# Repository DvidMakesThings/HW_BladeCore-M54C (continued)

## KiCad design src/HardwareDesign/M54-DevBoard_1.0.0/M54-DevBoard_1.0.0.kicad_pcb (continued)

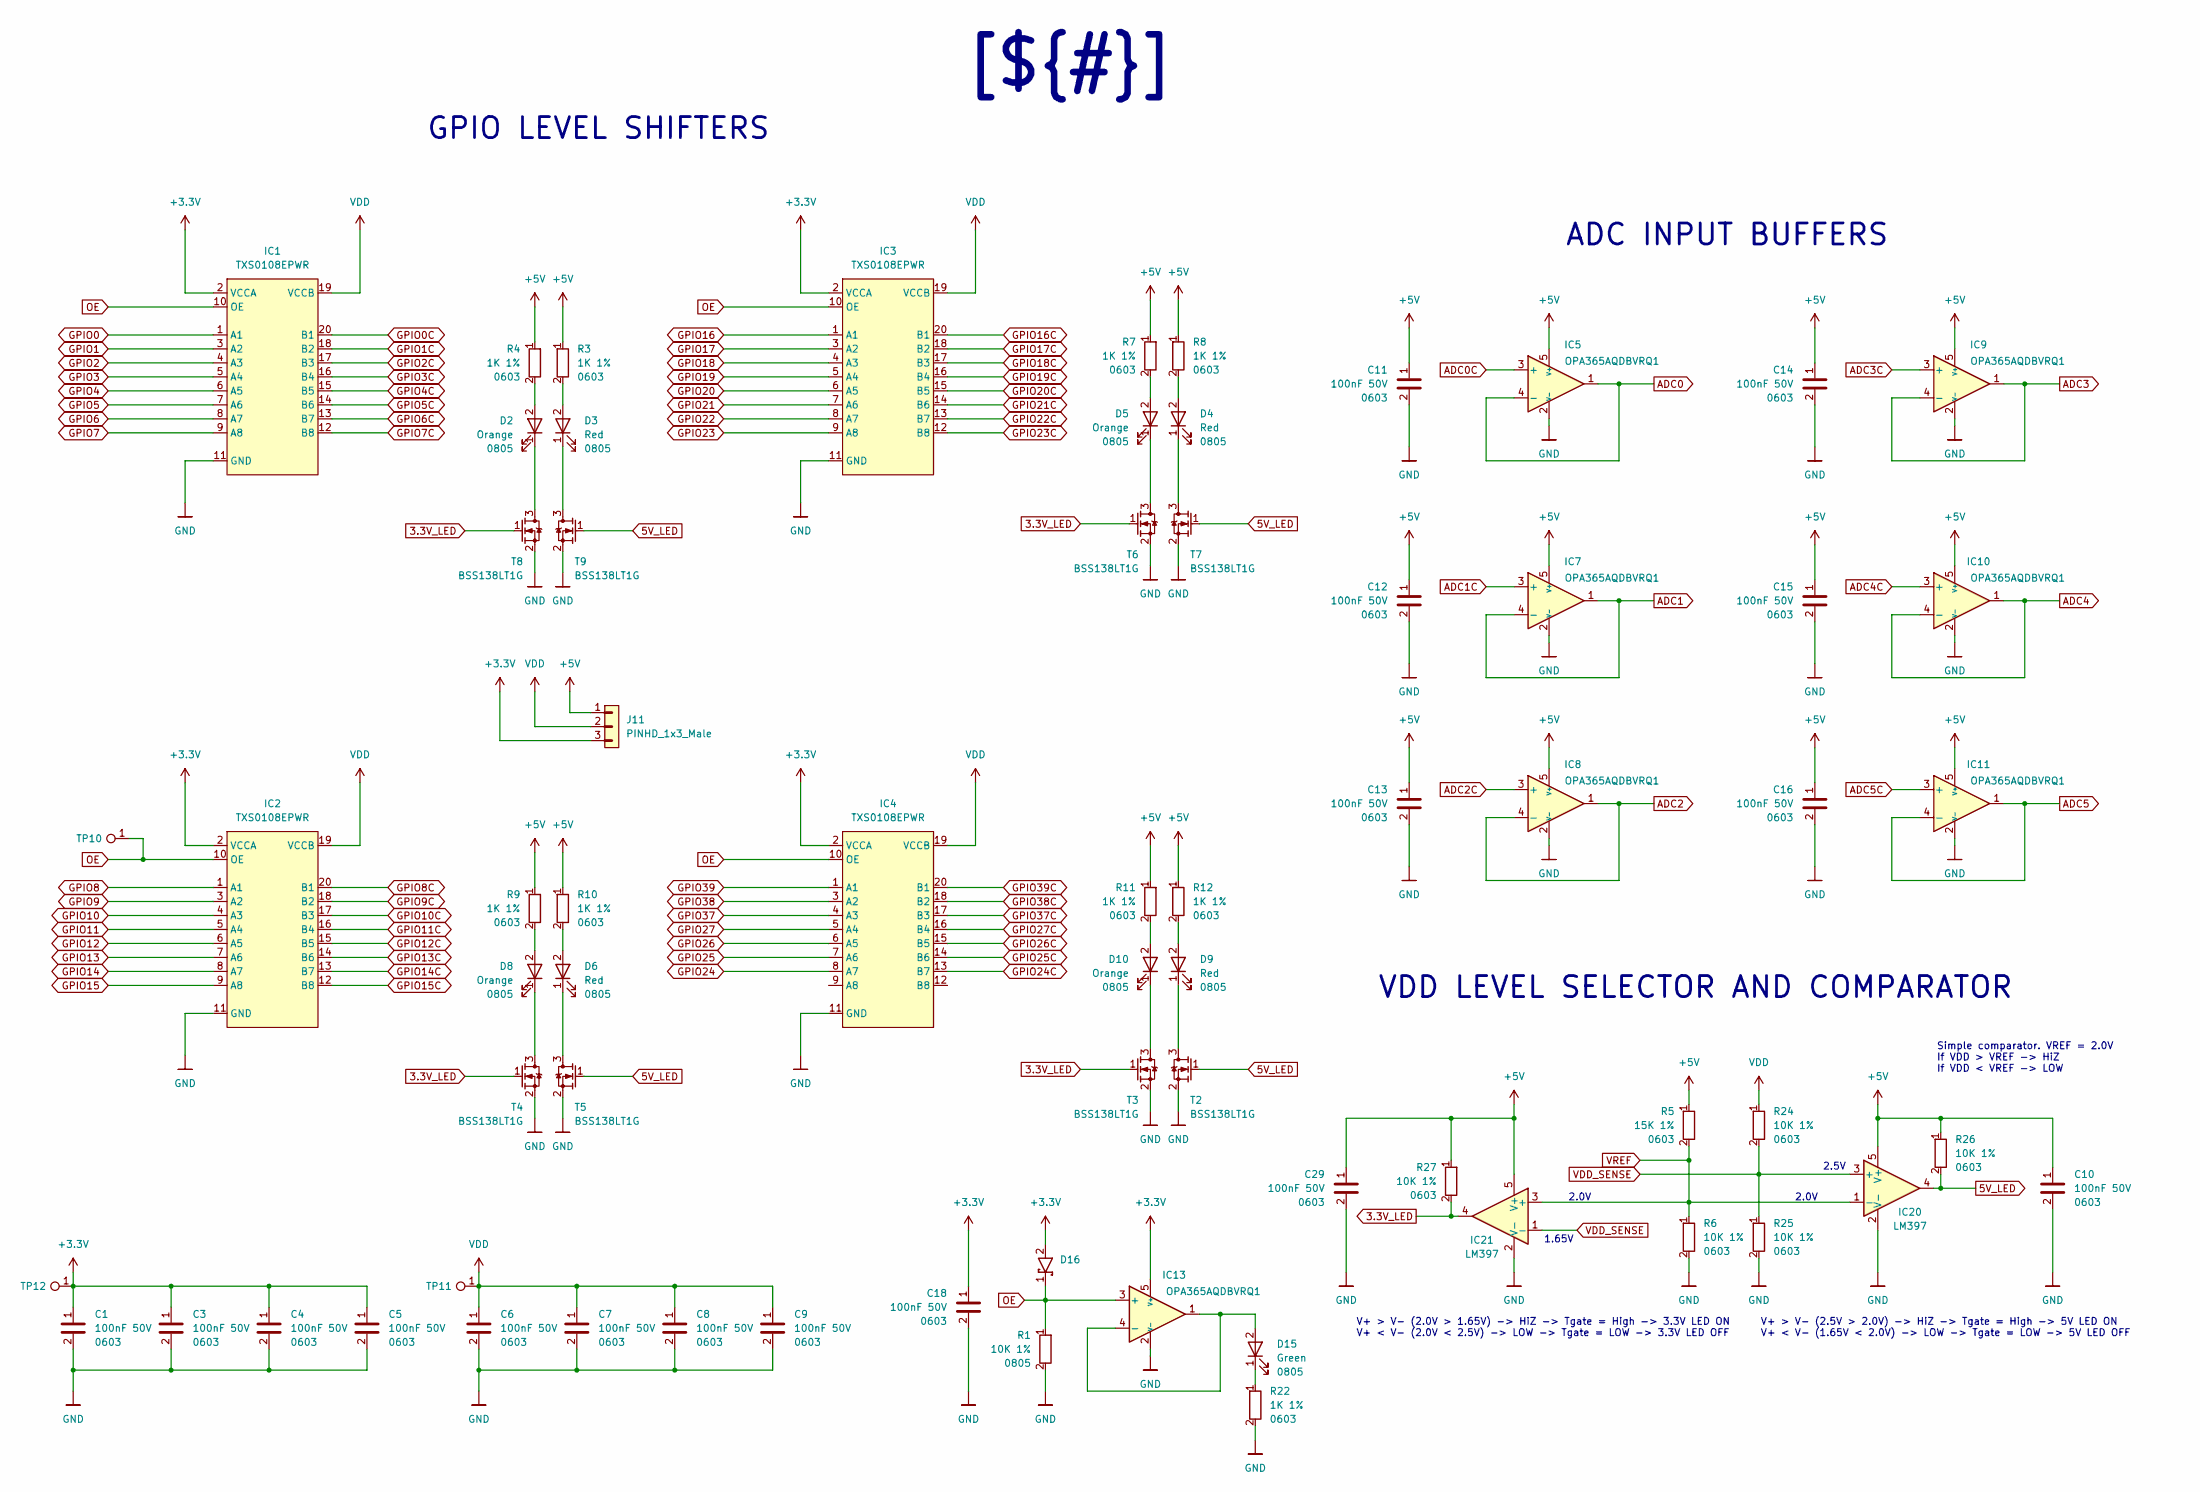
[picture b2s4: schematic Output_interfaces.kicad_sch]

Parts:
C1, C3, C4, C5, C6, C7, C8, C9, C10, C11, C12, C13, C14, C15, C16, C18, C29: 100nF 50V; C_0603_1608Metric; LCSC_PART C14663
D2, D5, D8, D10: Orange; LED_0805_2012Metric; MPN XL-2012UOC; LCSC_PART C965813
D3, D4, D6, D9: Red; LED_0805_2012Metric; MPN XL-2012VRC; LCSC_PART C7371913
D15: Green; LED_0805_2012Metric; MPN XL-2012UGC; LCSC_PART C965815
D16: SMA
IC1, IC2, IC3, IC4: TXS0108EPWR; TSSOP-20_4.4x6.5_P0.65mm; MPN TXS0108EPWR; LCSC_PART C17206
IC5, IC7, IC8, IC9, IC10, IC11, IC13: OPA365AQDBVRQ1; SOT-23-5; MPN OPA365AQDBVRQ1; LCSC_PART C485978
IC20, IC21: LM397; SOT-23-5
J11: PINHD_1x3_Male; PinHeader_1x03_P2.54mm_Vertical
R1: 10K 1%; R_0805_2012Metric; LCSC_PART C17414
R3, R4, R7, R8, R9, R10, R11, R12, R22: 1K 1%; R_0603_1608Metric; LCSC_PART C21190
R5: 15K 1%; R_0603_1608Metric; LCSC_PART C22809
R6, R24, R25, R26, R27: 10K 1%; R_0603_1608Metric; LCSC_PART C25804
T2, T3, T4, T5, T6, T7, T8, T9: BSS138LT1G; SOT-23; MPN BSS138LT1G
TP10, TP11, TP12: TestPoint_0.6mm

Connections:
3.3V_LED: IC21.4, R27.2, T3.1, T4.1, T6.1, T8.1
5V_LED: IC20.4, R26.2, T2.1, T5.1, T7.1, T9.1
+3.3V: C1.1, C3.1, C4.1, C5.1, C18.1, D16.2 (A), IC1.2 (VCCA), IC2.2 (VCCA), IC3.2 (VCCA), IC4.2 (VCCA), IC13.5 (V+), J11.3, TP12.1; also elsewhere on the board
+5V: C10.1, C11.1, C12.1, C13.1, C14.1, C15.1, C16.1, C29.1, IC5.5 (V+), IC7.5 (V+), IC8.5 (V+), IC9.5 (V+), IC10.5 (V+), IC11.5 (V+), IC20.5 (V+), IC21.5 (V+), J11.1, R3.1, R4.1, R5.1, R7.1, R8.1, R9.1, R10.1, R11.1, R12.1, R26.1, R27.1; also elsewhere on the board
ADC0: IC5.1, IC5.4 (-); also elsewhere on the board
ADC0C: IC5.3 (+); also elsewhere on the board
ADC1: IC7.1, IC7.4 (-); also elsewhere on the board
ADC1C: IC7.3 (+); also elsewhere on the board
ADC2: IC8.1, IC8.4 (-); also elsewhere on the board
ADC2C: IC8.3 (+); also elsewhere on the board
ADC3: IC9.1, IC9.4 (-); also elsewhere on the board
ADC3C: IC9.3 (+); also elsewhere on the board
ADC4: IC10.1, IC10.4 (-); also elsewhere on the board
ADC4C: IC10.3 (+); also elsewhere on the board
ADC5: IC11.1, IC11.4 (-); also elsewhere on the board
ADC5C: IC11.3 (+); also elsewhere on the board
GND: C1.2, C3.2, C4.2, C5.2, C6.2, C7.2, C8.2, C9.2, C10.2, C11.2, C12.2, C13.2, C14.2, C15.2, C16.2, C18.2, C29.2, IC1.11 (GND), IC2.11 (GND), IC3.11 (GND), IC4.11 (GND), IC5.2 (V-), IC7.2 (V-), IC8.2 (V-), IC9.2 (V-), IC10.2 (V-), IC11.2 (V-), IC13.2 (V-), IC20.2 (V-), IC21.2 (V-), R1.2, R6.2, R22.2, R25.2, T2.2, T3.2, T4.2, T5.2, T6.2, T7.2, T8.2, T9.2; also elsewhere on the board
GPIO0: IC1.1 (A1); also elsewhere on the board
GPIO0C: IC1.20 (B1); also elsewhere on the board
GPIO1: IC1.3 (A2); also elsewhere on the board
GPIO1C: IC1.18 (B2); also elsewhere on the board
GPIO2: IC1.4 (A3); also elsewhere on the board
GPIO2C: IC1.17 (B3); also elsewhere on the board
GPIO3: IC1.5 (A4); also elsewhere on the board
GPIO3C: IC1.16 (B4); also elsewhere on the board
GPIO4: IC1.6 (A5); also elsewhere on the board
GPIO4C: IC1.15 (B5); also elsewhere on the board
GPIO5: IC1.7 (A6); also elsewhere on the board
GPIO5C: IC1.14 (B6); also elsewhere on the board
GPIO6: IC1.8 (A7); also elsewhere on the board
GPIO6C: IC1.13 (B7); also elsewhere on the board
GPIO7: IC1.9 (A8); also elsewhere on the board
GPIO7C: IC1.12 (B8); also elsewhere on the board
GPIO8: IC2.1 (A1); also elsewhere on the board
GPIO8C: IC2.20 (B1); also elsewhere on the board
GPIO9: IC2.3 (A2); also elsewhere on the board
GPIO9C: IC2.18 (B2); also elsewhere on the board
GPIO10: IC2.4 (A3); also elsewhere on the board
GPIO10C: IC2.17 (B3); also elsewhere on the board
GPIO11: IC2.5 (A4); also elsewhere on the board
GPIO11C: IC2.16 (B4); also elsewhere on the board
GPIO12: IC2.6 (A5); also elsewhere on the board
GPIO12C: IC2.15 (B5); also elsewhere on the board
GPIO13: IC2.7 (A6); also elsewhere on the board
GPIO13C: IC2.14 (B6); also elsewhere on the board
GPIO14: IC2.8 (A7); also elsewhere on the board
GPIO14C: IC2.13 (B7); also elsewhere on the board
GPIO15: IC2.9 (A8); also elsewhere on the board
GPIO15C: IC2.12 (B8); also elsewhere on the board
GPIO16: IC3.1 (A1); also elsewhere on the board
GPIO16C: IC3.20 (B1); also elsewhere on the board
GPIO17: IC3.3 (A2); also elsewhere on the board
GPIO17C: IC3.18 (B2); also elsewhere on the board
GPIO18: IC3.4 (A3); also elsewhere on the board
GPIO18C: IC3.17 (B3); also elsewhere on the board
GPIO19: IC3.5 (A4); also elsewhere on the board
GPIO19C: IC3.16 (B4); also elsewhere on the board
GPIO20: IC3.6 (A5); also elsewhere on the board
GPIO20C: IC3.15 (B5); also elsewhere on the board
GPIO21: IC3.7 (A6); also elsewhere on the board
GPIO21C: IC3.14 (B6); also elsewhere on the board
GPIO22: IC3.8 (A7); also elsewhere on the board
GPIO22C: IC3.13 (B7); also elsewhere on the board
GPIO23: IC3.9 (A8); also elsewhere on the board
GPIO23C: IC3.12 (B8); also elsewhere on the board
GPIO24: IC4.8 (A7); also elsewhere on the board
GPIO24C: IC4.13 (B7); also elsewhere on the board
GPIO25: IC4.7 (A6); also elsewhere on the board
GPIO25C: IC4.14 (B6); also elsewhere on the board
GPIO26: IC4.6 (A5); also elsewhere on the board
GPIO26C: IC4.15 (B5); also elsewhere on the board
GPIO27: IC4.5 (A4); also elsewhere on the board
GPIO27C: IC4.16 (B4); also elsewhere on the board
GPIO37: IC4.4 (A3); also elsewhere on the board
GPIO37C: IC4.17 (B3); also elsewhere on the board
GPIO38: IC4.3 (A2); also elsewhere on the board
GPIO38C: IC4.18 (B2); also elsewhere on the board
GPIO39: IC4.1 (A1); also elsewhere on the board
GPIO39C: IC4.20 (B1); also elsewhere on the board
unnamed: D2.1, T8.3
unnamed: D2.2, R4.2
unnamed: D3.1, T9.3
unnamed: D3.2, R3.2
unnamed: D4.1, T7.3
unnamed: D4.2, R8.2
unnamed: D5.1, T6.3
unnamed: D5.2, R7.2
unnamed: D6.1, T5.3
unnamed: D6.2, R10.2
unnamed: D8.1, T4.3
unnamed: D8.2, R9.2
unnamed: D9.1, T2.3
unnamed: D9.2, R12.2
unnamed: D10.1, T3.3
unnamed: D10.2, R11.2
unnamed: D15.1, R22.1
unnamed: D15.2, IC13.1, IC13.4 (-)
OE: D16.1 (K), IC1.10 (OE), IC2.10 (OE), IC3.10 (OE), IC4.10 (OE), IC13.3 (+), R1.1, TP10.1
VDD: C6.1, C7.1, C8.1, C9.1, IC1.19 (VCCB), IC2.19 (VCCB), IC3.19 (VCCB), IC4.19 (VCCB), J11.2, R24.1, TP11.1; also elsewhere on the board
VDD_SENSE: IC20.3 (+), IC21.1 (-), R24.2, R25.1
VREF: IC20.1 (-), IC21.3 (+), R5.2, R6.1

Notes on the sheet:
2.0V
Simple comparator. VREF = 2.0V If VDD > VREF -> HiZ If VDD < VREF -> LOW
VDD LEVEL SELECTOR AND COMPARATOR
GPIO LEVEL SHIFTERS
1.65V
2.5V
ADC INPUT BUFFERS
V+ > V- (2.0V > 1.65V) -> HiZ -> Tgate = High -> 3.3V LED ON V+ < V- (2.0V < 2.5V) -> LOW -> Tgate = LOW -> 3.3V LED OFF
V+ > V- (2.5V > 2.0V) -> HiZ -> Tgate = High -> 5V LED ON V+ < V- (1.65V < 2.0V) -> LOW -> Tgate = LOW -> 5V LED OFF
[${#}] ${TITLE}

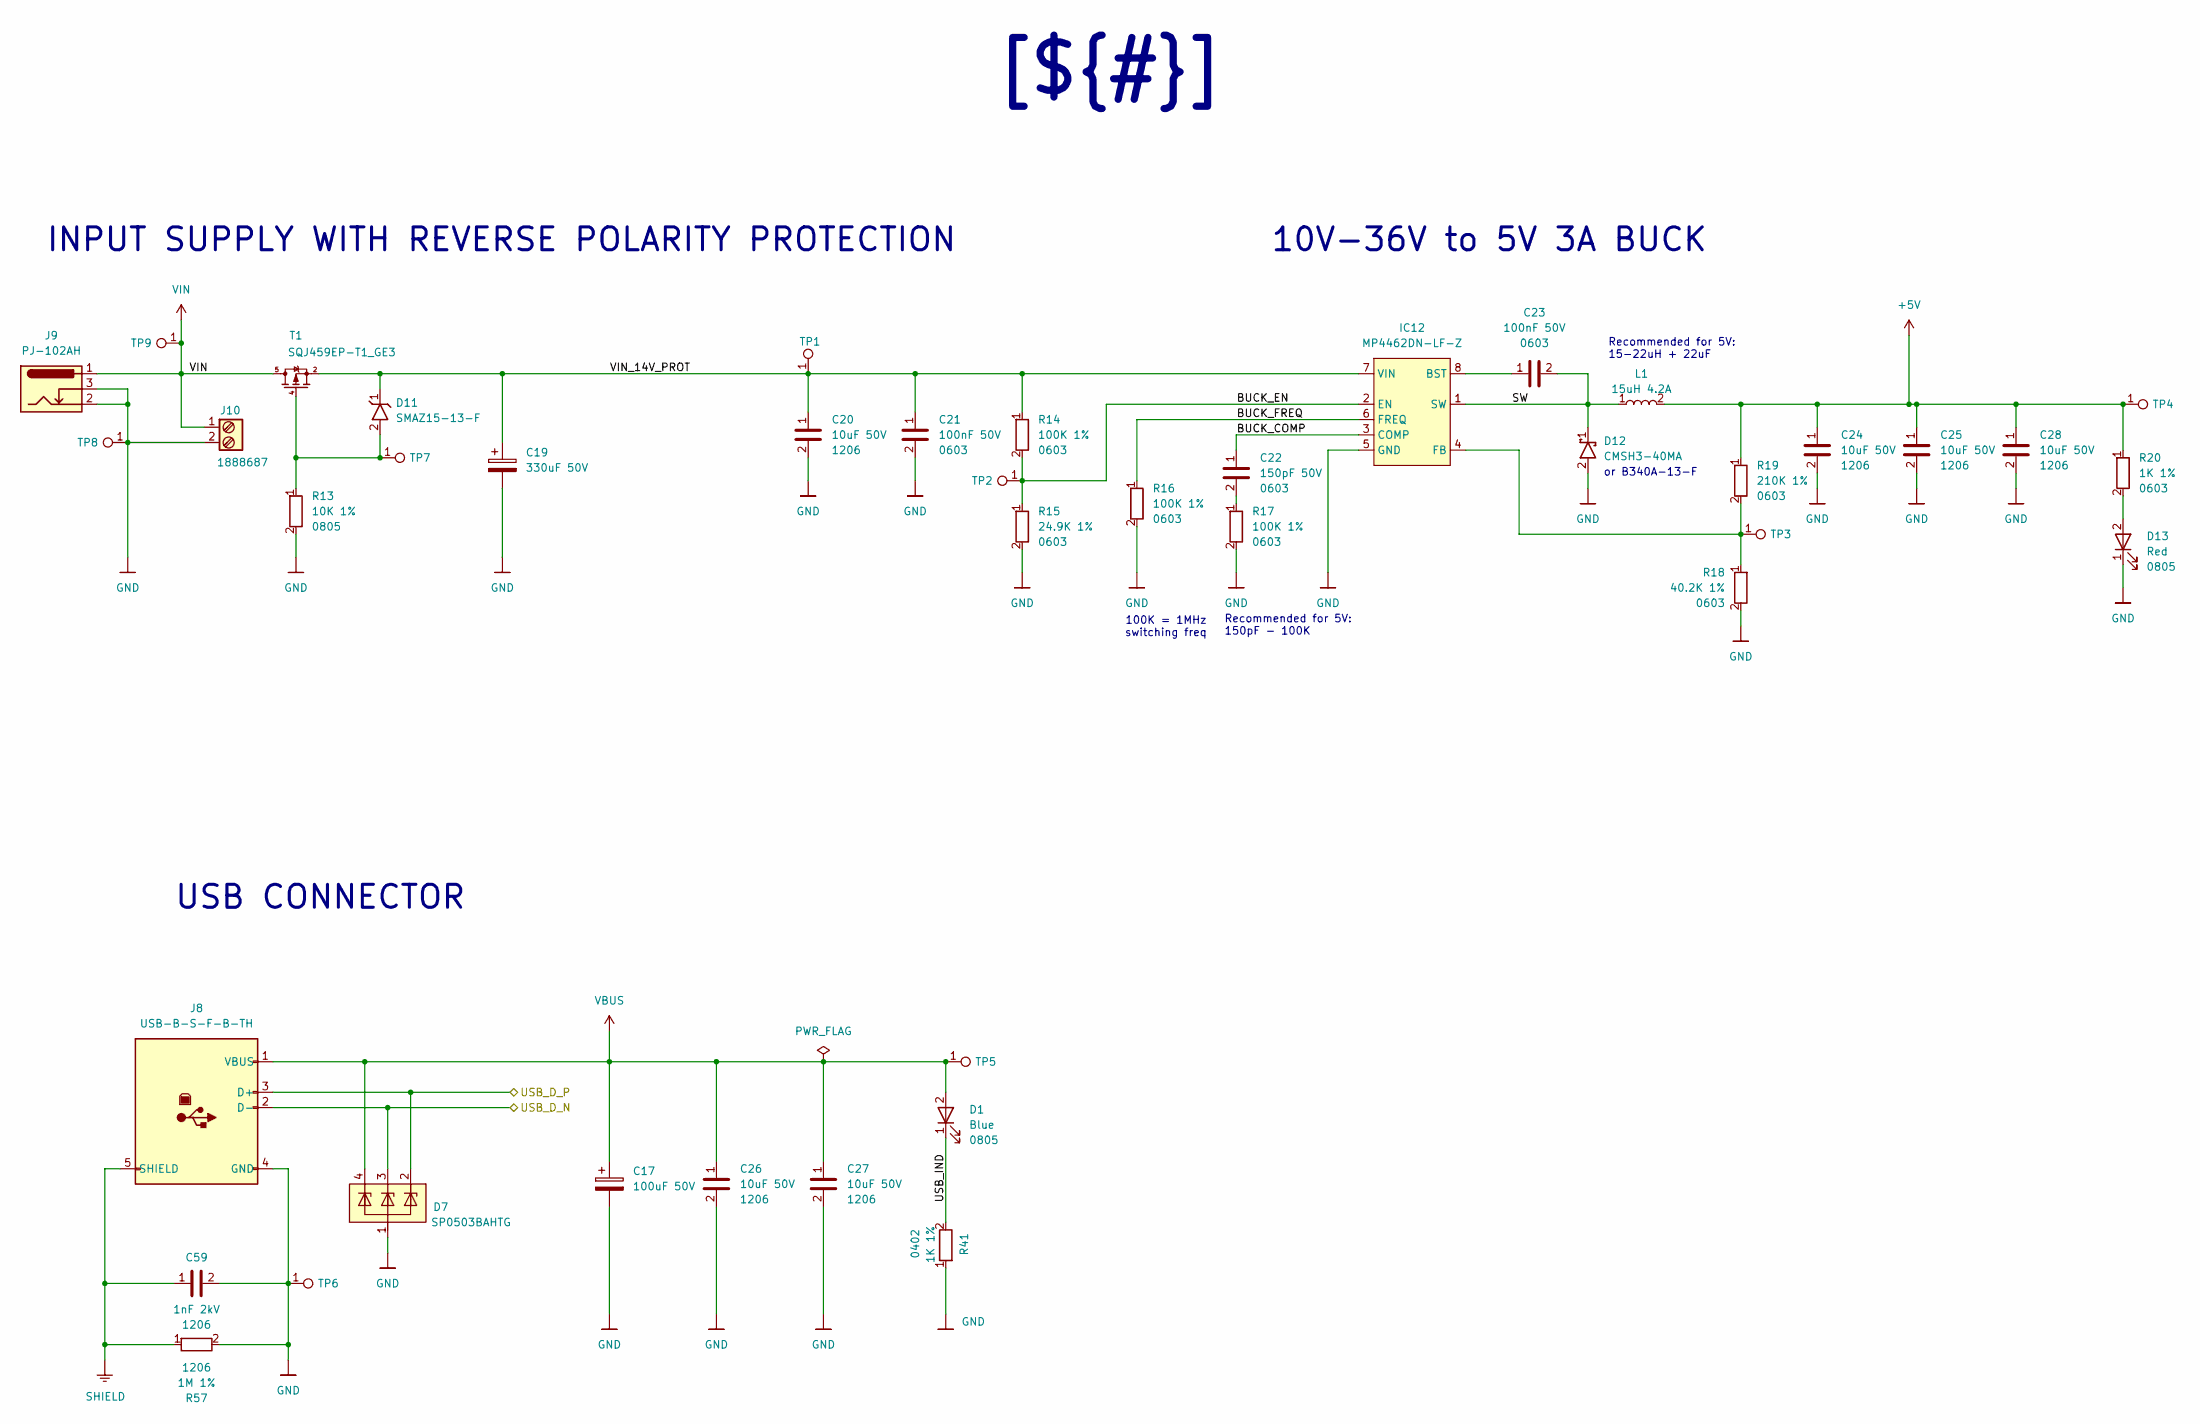
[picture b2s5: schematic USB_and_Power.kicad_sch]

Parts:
C17: 100uF 50V; C_Elec_6.3x7.7; MPN RVT1H101M0607; LCSC_PART C3151829
C19: 330uF 50V; CP_Elec_10x10.5; MPN EEE-FT1H331AP; LCSC_PART C178596
C20, C24, C25, C26, C27, C28: 10uF 50V; C_1206_3216Metric; MPN CL31A106KBHNNNE; LCSC_PART C13585
C21, C23: 100nF 50V; C_0603_1608Metric; LCSC_PART C14663
C22: 150pF 50V; C_0603_1608Metric; MPN 0603B151K500NT; LCSC_PART C1594
C59: 1nF 2kV; C_1206_3216Metric; LCSC_PART C173242
D1: Blue; LED_0603_1608Metric; MPN XL-2012UBC; LCSC_PART C965817
D7: SP0503BAHTG; SOT143; MPN SP0503BAHTG; LCSC_PART C3040626
D11: SMAZ15-13-F; SMA; MPN SMAZ15-13-F; LCSC_PART C110524
D12: CMSH3-40MA; SMA; MPN CMSH3-40MA TR13 PBFREE; LCSC_PART C48937470
D13: Red; LED_0805_2012Metric; MPN XL-2012VRC; LCSC_PART C7371913
IC12: MP4462DN-LF-Z; SO-8_3.9x4.9mm_EP2.6x3.5mm; MPN MCP1754ST-3302E/MB; LCSC_PART C28398
J8: USB-B-S-F-B-TH; USB_B_Lumberg_2411_02_Horizontal; MPN USB-B-S-F-B-TH; LCSC_PART C5714571
J9: PJ-102AH; BarrelJack_CUI_PJ-102AH_Horizontal; MPN PJ-102AH; LCSC_PART C3096093
J10: 1888687; TerminalBlock_Phoenix_PT-1,5-2-5.0-H_1x02_P5.00mm_Horizontal
L1: 15uH 4.2A; L_12x12x6_WE-PD-1260; MPN 744771115; LCSC_PART C2049359
R13: 10K 1%; R_0805_2012Metric; LCSC_PART C17414
R14, R16, R17: 100K 1%; R_0603_1608Metric; LCSC_PART C25803
R15: 24.9K 1%; R_0603_1608Metric; LCSC_PART C2930080
R18: 40.2K 1%; R_0603_1608Metric; LCSC_PART C12447
R19: 210K 1%; R_0603_1608Metric; MPN 0603WAF2103T5E; LCSC_PART C22952
R20: 1K 1%; R_0603_1608Metric; LCSC_PART C21190
R41: 1K 1%; R_0402_1005Metric; LCSC_PART C11702
R57: 1M 1%; R_1206_3216Metric; LCSC_PART C17927
SHIELD1: SHIELD
T1: SQJ459EP-T1_GE3; PowerPAK SO-8; MPN SQJ459EP-T1_GE3; LCSC_PART C3289501
TP1, TP2, TP3, TP4, TP5, TP6, TP7, TP8, TP9: TestPoint_0.6mm

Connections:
+5V: C24.1, C25.1, C28.1, L1.2, R19.1, R20.1, TP4.1; also elsewhere on the board
/Project Architecture/Bladecore M54C/USB_D_N: D7.3, J8.2 (D-); also elsewhere on the board
/Project Architecture/Bladecore M54C/USB_D_P: D7.2, J8.3 (D+); also elsewhere on the board
/Project Architecture/USB and Power/BUCK_COMP: C22.1, IC12.3 (COMP)
/Project Architecture/USB and Power/BUCK_EN: IC12.2 (EN), R14.2, R15.1, TP2.1
/Project Architecture/USB and Power/BUCK_FREQ: IC12.6 (FREQ), R16.1
/Project Architecture/USB and Power/SW: C23.2, D12.1 (K), IC12.1 (SW), L1.1
/Project Architecture/USB and Power/USB_IND: D1.1, R41.2
/Project Architecture/USB and Power/VIN_14V_PROT: C19.1, C20.1, C21.1, D11.1 (K), IC12.7 (VIN), R14.1, T1.1 (S), T1.2 (S), T1.3 (S), TP1.1
GND: C17.2, C19.2, C20.2, C21.2, C24.2, C25.2, C26.2, C27.2, C28.2, C59.2, D7.1, D12.2 (A), D13.1, IC12.5 (GND), IC12.9 (EP), J8.4 (GND), J9.2, J9.3, J10.2, R13.2, R15.2, R16.2, R17.2, R18.2, R41.1, R57.2, TP6.1, TP8.1; also elsewhere on the board
unnamed: C22.2, R17.1
unnamed: D11.2 (A), R13.1, T1.4 (G), TP7.1
unnamed: D13.2, R20.2
unnamed: C23.1, IC12.8 (BST)
unnamed: IC12.4 (FB), R18.1, R19.2, TP3.1
VBUS: C17.1, C26.1, C27.1, D1.2, D7.4, J8.1 (VBUS), TP5.1; also elsewhere on the board
VIN: J9.1, J10.1, T1.5 (D), T1.6 (D), T1.7 (D), T1.8 (D), TP9.1; also elsewhere on the board

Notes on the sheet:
Recommended for 5V: 15-22uH + 22uF
10V-36V to 5V 3A BUCK
INPUT SUPPLY WITH REVERSE POLARITY PROTECTION
100K = 1MHz switching freq
or B340A-13-F
USB CONNECTOR
Recommended for 5V: 150pF - 100K
[${#}] ${TITLE}

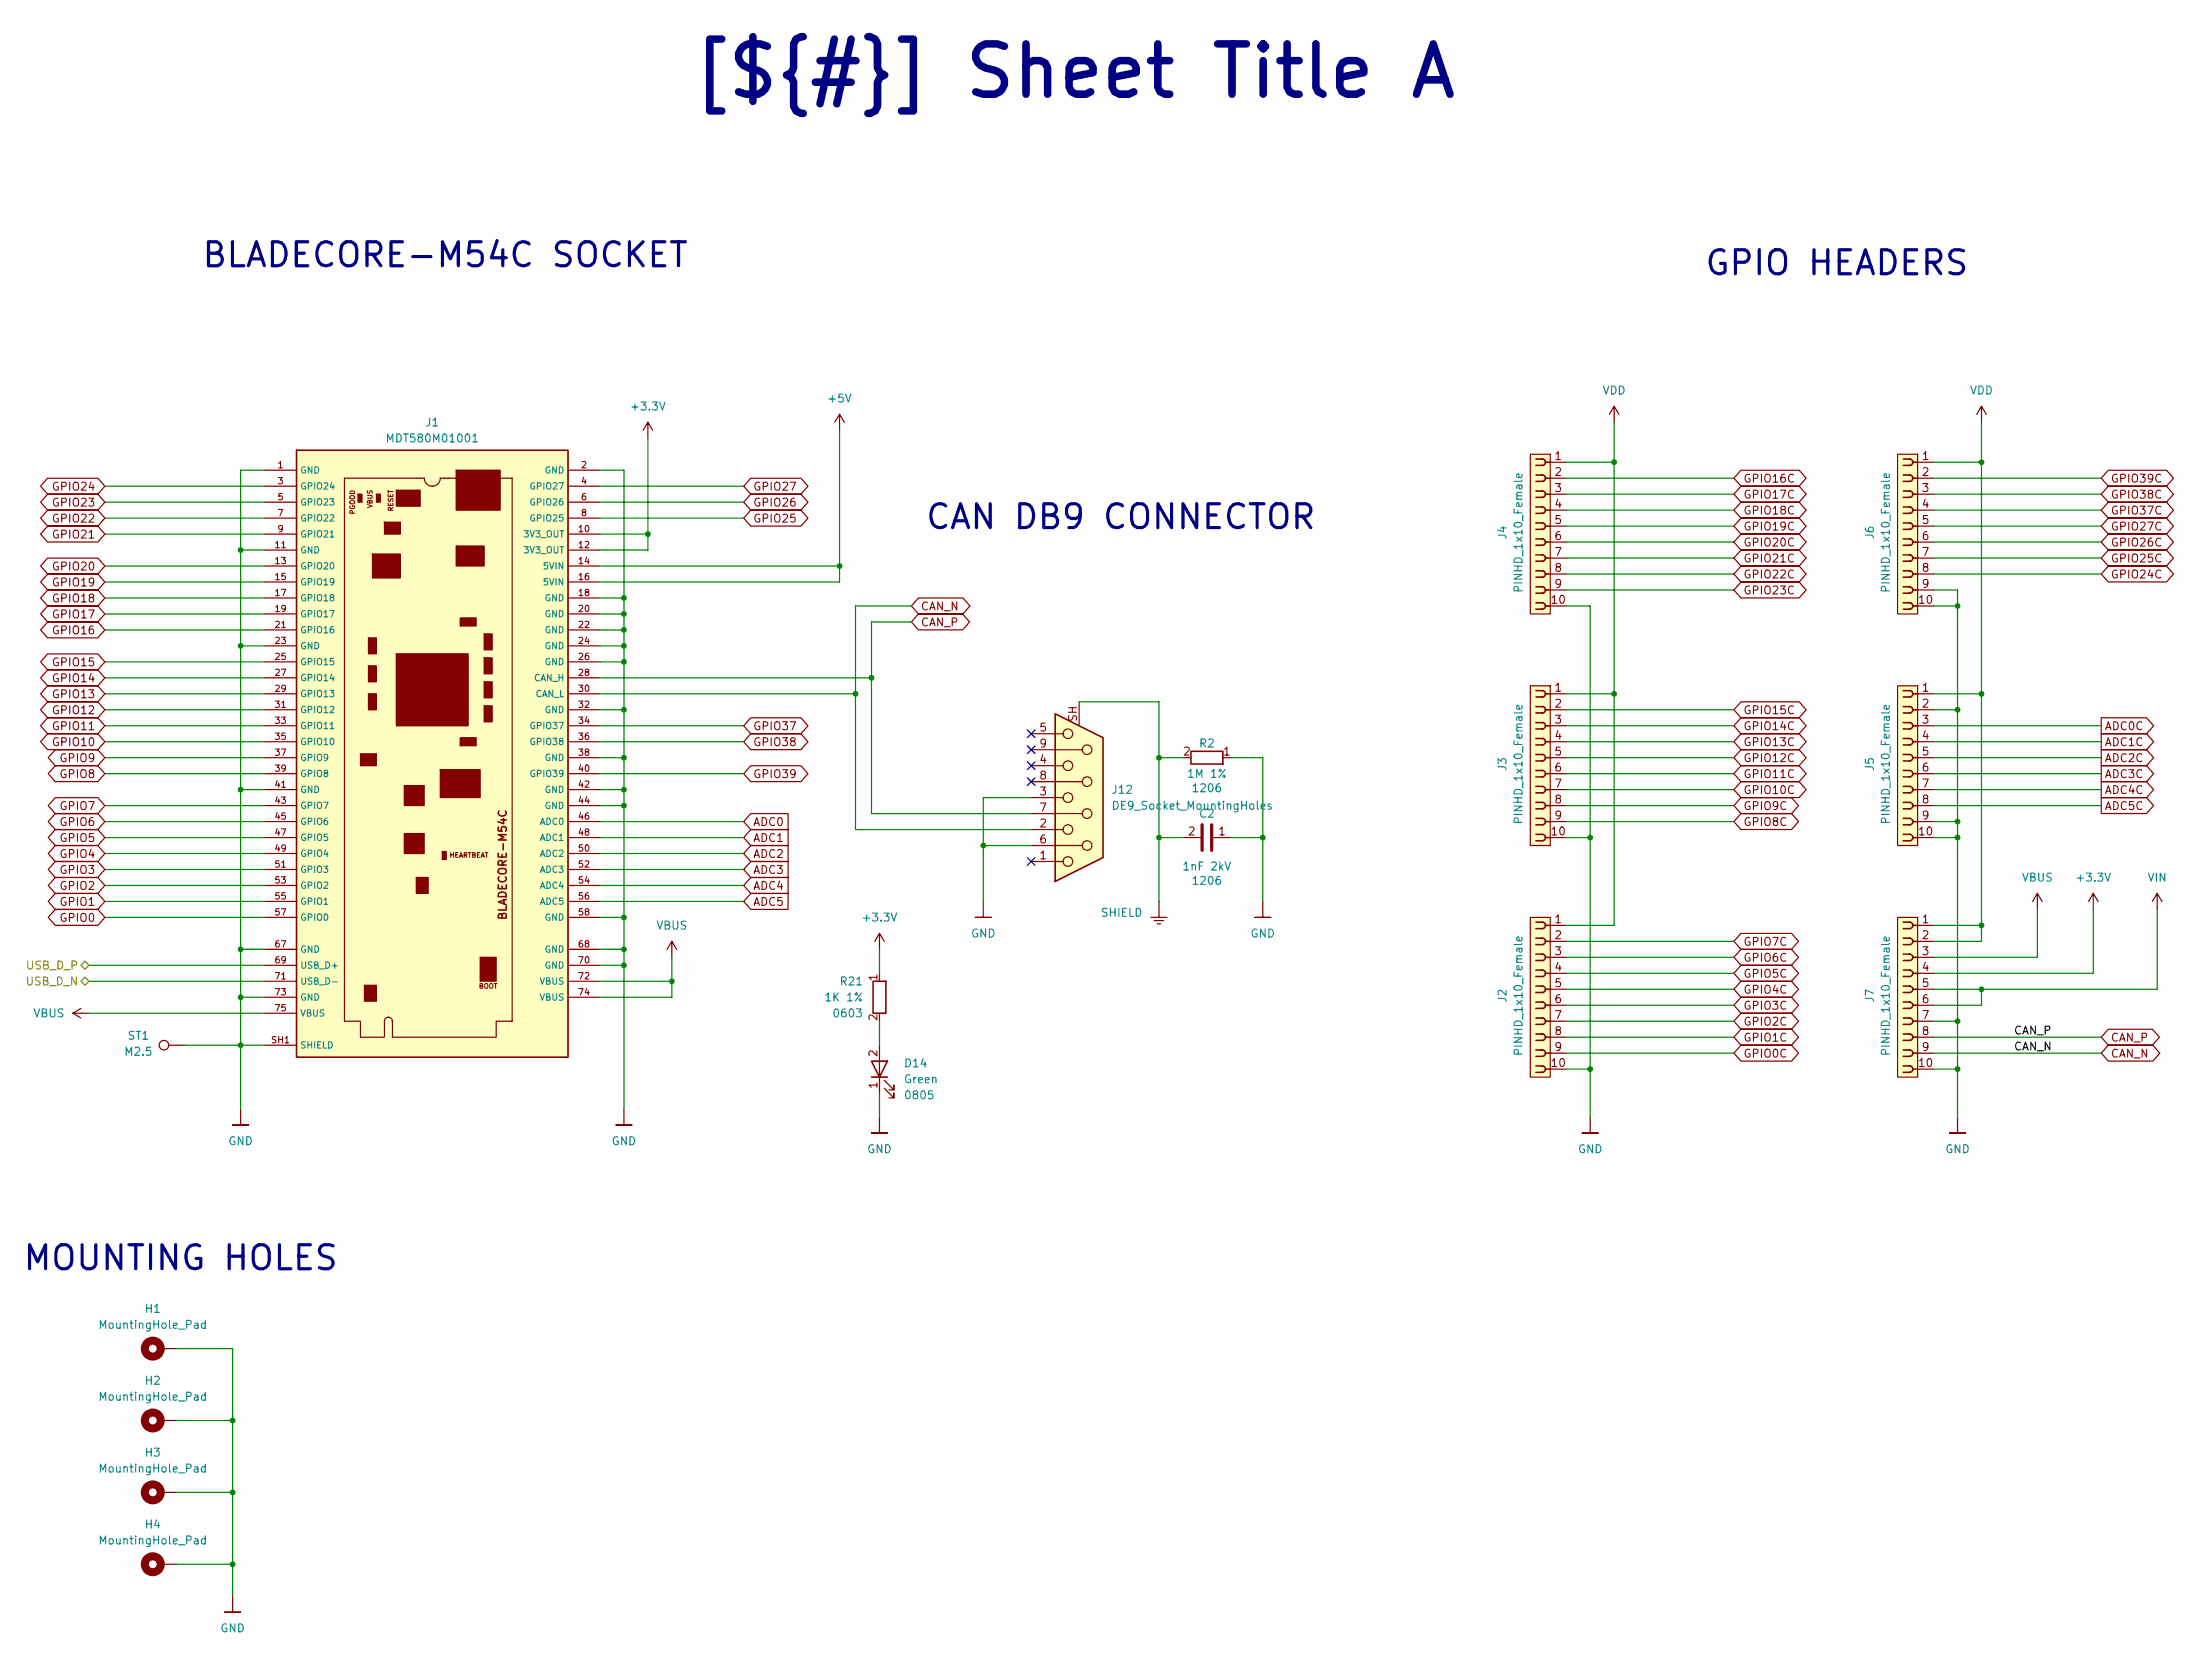
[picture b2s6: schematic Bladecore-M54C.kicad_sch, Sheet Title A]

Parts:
C2: 1nF 2kV; C_1206_3216Metric; LCSC_PART C173242
D14: Green; LED_0805_2012Metric; MPN XL-2012UGC; LCSC_PART C965815
H1, H2, H3, H4: MountingHole_Pad; MountingHole_3.2mm_M3_Pad_Via
J1: MDT580M01001; BladeCore-M54C; MPN MDT580M01001; LCSC_PART C5177196
J2, J3, J4, J5, J6, J7: PINHD_1x10_Female; PinSocket_1x10_P2.54mm_Vertical
J12: DE9_Socket_MountingHoles; DSUB-9_Socket_Horizontal_P2.77x2.84mm_EdgePinOffset7.70mm_H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
R2: 1M 1%; R_1206_3216Metric; LCSC_PART C17927
R21: 1K 1%; R_0603_1608Metric; LCSC_PART C21190
SHIELD2: SHIELD
ST1: M2.5; Round Standoff Threaded M2.5 Steel; MPN 9774045151R; LCSC_PART C7435234

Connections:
+3.3V: J1.10 (3V3_OUT), J1.12 (3V3_OUT), J7.4, R21.1; also elsewhere on the board
+5V: J1.14 (5VIN), J1.16 (5VIN); also elsewhere on the board
/Project Architecture/Bladecore M54C/USB_D_N: J1.71 (USB_D-); also elsewhere on the board
/Project Architecture/Bladecore M54C/USB_D_P: J1.69 (USB_D+); also elsewhere on the board
ADC0: J1.46 (ADC0); also elsewhere on the board
ADC0C: J5.3; also elsewhere on the board
ADC1: J1.48 (ADC1); also elsewhere on the board
ADC1C: J5.4; also elsewhere on the board
ADC2: J1.50 (ADC2); also elsewhere on the board
ADC2C: J5.5; also elsewhere on the board
ADC3: J1.52 (ADC3); also elsewhere on the board
ADC3C: J5.6; also elsewhere on the board
ADC4: J1.54 (ADC4); also elsewhere on the board
ADC4C: J5.7; also elsewhere on the board
ADC5: J1.56 (ADC5); also elsewhere on the board
ADC5C: J5.8; also elsewhere on the board
CAN_N: J1.30 (CAN_L), J7.9, J12.2
CAN_P: J1.28 (CAN_H), J7.8, J12.7
GND: C2.1, D14.1, H1.1 (1_1), H2.1 (1_1), H3.1 (1_1), H4.1 (1_1), J1.1 (GND), J1.2 (GND), J1.11 (GND), J1.18 (GND), J1.20 (GND), J1.22 (GND), J1.23 (GND), J1.24 (GND), J1.26 (GND), J1.32 (GND), J1.38 (GND), J1.41 (GND), J1.42 (GND), J1.44 (GND), J1.58 (GND), J1.67 (GND), J1.68 (GND), J1.70 (GND), J1.73 (GND), J1.SH1 (SHIELD), J1.SH2 (SHIELD), J2.10, J3.10, J4.10, J5.2, J5.9, J5.10, J6.9, J6.10, J7.7, J7.10, J12.3, J12.6, R2.1, ST1.1; also elsewhere on the board
GPIO0: J1.57 (GPIO0); also elsewhere on the board
GPIO0C: J2.9; also elsewhere on the board
GPIO1: J1.55 (GPIO1); also elsewhere on the board
GPIO1C: J2.8; also elsewhere on the board
GPIO2: J1.53 (GPIO2); also elsewhere on the board
GPIO2C: J2.7; also elsewhere on the board
GPIO3: J1.51 (GPIO3); also elsewhere on the board
GPIO3C: J2.6; also elsewhere on the board
GPIO4: J1.49 (GPIO4); also elsewhere on the board
GPIO4C: J2.5; also elsewhere on the board
GPIO5: J1.47 (GPIO5); also elsewhere on the board
GPIO5C: J2.4; also elsewhere on the board
GPIO6: J1.45 (GPIO6); also elsewhere on the board
GPIO6C: J2.3; also elsewhere on the board
GPIO7: J1.43 (GPIO7); also elsewhere on the board
GPIO7C: J2.2; also elsewhere on the board
GPIO8: J1.39 (GPIO8); also elsewhere on the board
GPIO8C: J3.9; also elsewhere on the board
GPIO9: J1.37 (GPIO9); also elsewhere on the board
GPIO9C: J3.8; also elsewhere on the board
GPIO10: J1.35 (GPIO10); also elsewhere on the board
GPIO10C: J3.7; also elsewhere on the board
GPIO11: J1.33 (GPIO11); also elsewhere on the board
GPIO11C: J3.6; also elsewhere on the board
GPIO12: J1.31 (GPIO12); also elsewhere on the board
GPIO12C: J3.5; also elsewhere on the board
GPIO13: J1.29 (GPIO13); also elsewhere on the board
GPIO13C: J3.4; also elsewhere on the board
GPIO14: J1.27 (GPIO14); also elsewhere on the board
GPIO14C: J3.3; also elsewhere on the board
GPIO15: J1.25 (GPIO15); also elsewhere on the board
GPIO15C: J3.2; also elsewhere on the board
GPIO16: J1.21 (GPIO16); also elsewhere on the board
GPIO16C: J4.2; also elsewhere on the board
GPIO17: J1.19 (GPIO17); also elsewhere on the board
GPIO17C: J4.3; also elsewhere on the board
GPIO18: J1.17 (GPIO18); also elsewhere on the board
GPIO18C: J4.4; also elsewhere on the board
GPIO19: J1.15 (GPIO19); also elsewhere on the board
GPIO19C: J4.5; also elsewhere on the board
GPIO20: J1.13 (GPIO20); also elsewhere on the board
GPIO20C: J4.6; also elsewhere on the board
GPIO21: J1.9 (GPIO21); also elsewhere on the board
GPIO21C: J4.7; also elsewhere on the board
GPIO22: J1.7 (GPIO22); also elsewhere on the board
GPIO22C: J4.8; also elsewhere on the board
GPIO23: J1.5 (GPIO23); also elsewhere on the board
GPIO23C: J4.9; also elsewhere on the board
GPIO24: J1.3 (GPIO24); also elsewhere on the board
GPIO24C: J6.8; also elsewhere on the board
GPIO25: J1.8 (GPIO25); also elsewhere on the board
GPIO25C: J6.7; also elsewhere on the board
GPIO26: J1.6 (GPIO26); also elsewhere on the board
GPIO26C: J6.6; also elsewhere on the board
GPIO27: J1.4 (GPIO27); also elsewhere on the board
GPIO27C: J6.5; also elsewhere on the board
GPIO37: J1.34 (GPIO37); also elsewhere on the board
GPIO37C: J6.4; also elsewhere on the board
GPIO38: J1.36 (GPIO38); also elsewhere on the board
GPIO38C: J6.3; also elsewhere on the board
GPIO39: J1.40 (GPIO39); also elsewhere on the board
GPIO39C: J6.2; also elsewhere on the board
unnamed: D14.2, R21.2
VBUS: J1.72 (VBUS), J1.74 (VBUS), J1.75 (VBUS), J7.3; also elsewhere on the board
VDD: J2.1, J3.1, J4.1, J5.1, J6.1, J7.1, J7.2; also elsewhere on the board
VIN: J7.5, J7.6; also elsewhere on the board

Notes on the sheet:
MOUNTING HOLES
BLADECORE-M54C SOCKET
GPIO HEADERS
CAN DB9 CONNECTOR
[${#}] ${TITLE}

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
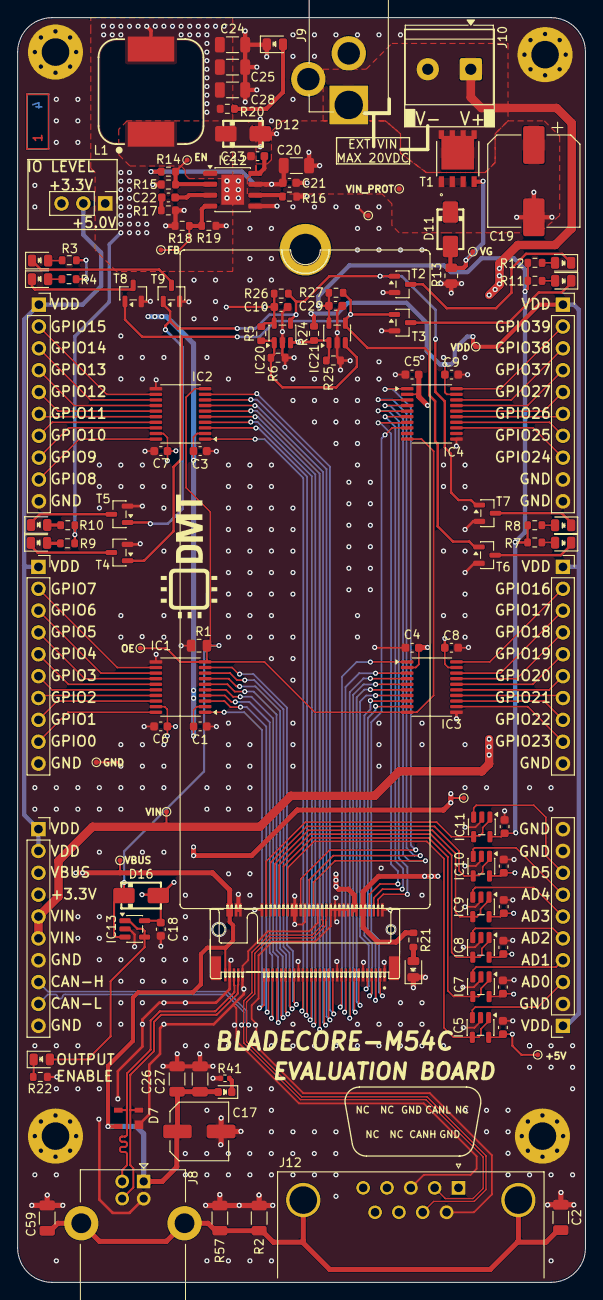
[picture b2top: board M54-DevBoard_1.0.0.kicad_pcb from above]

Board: 4 copper layers, 66.0 x 147.0 mm, 127 parts (0 on the bottom side), 120 nets.

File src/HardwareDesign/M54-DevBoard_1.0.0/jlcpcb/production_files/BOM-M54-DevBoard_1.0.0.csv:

Comment,Designator,Footprint,LCSC,Quantity
100K 1%,"R14,R16,R17",R_0603_1608Metric,C25803,3
100nF 50V,"C1,C10,C11,C12,C13,C14,C15,C16,C18,C21,C23,C29,C3,C4,C5,C6,C7,C8,C9",C_0603_1608Metric,C14663,19
100uF 50V,C17,C_Elec_6.3x7.7,C3151829,1
10K 1%,"R1,R13",R_0805_2012Metric,C17414,2
10K 1%,"R24,R25,R26,R27,R6",R_0603_1608Metric,C25804,5
10uF 50V,"C20,C24,C25,C26,C27,C28",C_1206_3216Metric,C13585,6
150pF 50V,C22,C_0603_1608Metric,C1594,1
15K 1%,R5,R_0603_1608Metric,C22809,1
15uH 4.2A,L1,L_12x12x6_WE-PD-1260,C2049359,1
1K 1%,R41,R_0402_1005Metric,C11702,1
1K 1%,"R10,R11,R12,R20,R21,R22,R3,R4,R7,R8,R9",R_0603_1608Metric,C21190,11
1M 1%,"R2,R57",R_1206_3216Metric,C17927,2
1nF 2kV,"C2,C59",C_1206_3216Metric,C173242,2
210K 1%,R19,R_0603_1608Metric,C22952,1
24.9K 1%,R15,R_0603_1608Metric,C2930080,1
330uF 50V,C19,CP_Elec_10x10.5,C178596,1
40.2K 1%,R18,R_0603_1608Metric,C12447,1
Blue,D1,LED_0603_1608Metric,C965817,1
CMSH3-40MA,D12,SMA,C48937470,1
Green,"D14,D15",LED_0805_2012Metric,C965815,2
M2.5,ST1,Round Standoff Threaded M2.5 Steel,C7435234,1
MP4462DN-LF-Z,IC12,SO-8_3.9x4.9mm_EP2.6x3.5mm,C28398,1
OPA365AQDBVRQ1,"IC10,IC11,IC13,IC5,IC7,IC8,IC9",SOT-23-5,C485978,7
Orange,"D10,D2,D5,D8",LED_0805_2012Metric,C965813,4
PJ-102AH,J9,BarrelJack_CUI_PJ-102AH_Horizontal,C3096093,1
Red,"D13,D3,D4,D6,D9",LED_0805_2012Metric,C7371913,5
SMAZ15-13-F,D11,SMA,C110524,1
SP0503BAHTG,D7,SOT143,C3040626,1
SQJ459EP-T1_GE3,T1,PowerPAK SO-8,C3289501,1
TXS0108EPWR,"IC1,IC2,IC3,IC4",TSSOP-20_4.4x6.5_P0.65mm,C17206,4
USB-B-S-F-B-TH,J8,USB_B_Lumberg_2411_02_Horizontal,C5714571,1
LM397,IC21,SOT-23-5,,1
LM397,IC20,SOT-23-5,,1
PINHD_1x10_Female,J3,PinSocket_1x10_P2.54mm_Vertical,,1
PINHD_1x10_Female,J4,PinSocket_1x10_P2.54mm_Vertical,,1
PINHD_1x10_Female,J5,PinSocket_1x10_P2.54mm_Vertical,,1
PINHD_1x10_Female,J7,PinSocket_1x10_P2.54mm_Vertical,,1
BSS138LT1G,T2,SOT-23,,1
BSS138LT1G,T3,SOT-23,,1
BSS138LT1G,T4,SOT-23,,1
BSS138LT1G,T5,SOT-23,,1
BSS138LT1G,T6,SOT-23,,1
BSS138LT1G,T7,SOT-23,,1
BSS138LT1G,T8,SOT-23,,1
~,TP1,TestPoint_0.6mm,,1
~,TP2,TestPoint_0.6mm,,1
~,TP3,TestPoint_0.6mm,,1
~,TP4,TestPoint_0.6mm,,1
~,TP5,TestPoint_0.6mm,,1
~,TP7,TestPoint_0.6mm,,1
~,TP8,TestPoint_0.6mm,,1
~,TP9,TestPoint_0.6mm,,1
~,TP10,TestPoint_0.6mm,,1
~,TP11,TestPoint_0.6mm,,1
~,TP12,TestPoint_0.6mm,,1
PINHD_1x10_Female,J6,PinSocket_1x10_P2.54mm_Vertical,,1
~,TP6,TestPoint_0.6mm,,1
BSS138LT1G,T9,SOT-23,,1
DE9_Socket_MountingHoles,J12,DSUB-9_Socket_Horizontal_P2.77x2.84mm_EdgePinOffset7.70mm_Housed_MountingHolesOffset9.12mm,,1
PINHD_1x3_Male,J11,PinHeader_1x03_P2.54mm_Vertical,,1
1888687,J10,"TerminalBlock_Phoenix_PT-1,5-2-5.0-H_1x02_P5.00mm_Horizontal",,1
PINHD_1x10_Female,J2,PinSocket_1x10_P2.54mm_Vertical,,1
~,D16,SMA,,1

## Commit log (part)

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2026-02-18 first release
2026-02-18 add production files
2026-02-18 update component list
2026-03-19 Update M54C
2026-03-19 Update pdf schematic
2026-03-19 Finalize design
2026-03-19 add simple software
2026-03-21 add eval board
2026-03-21 export gerbers
2026-03-21 add images
2026-03-21 add manual
2026-03-23 Generate pdf
2026-04-07 fix hardware bugs, add software example
2026-04-08 scope measurements
2026-04-10 correct devboard findings
2026-05-31 update documentation
